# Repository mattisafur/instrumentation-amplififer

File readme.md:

# Tiny Instrumentation Amplififer

This is a small challenge I gave myself, trying to design an opamp based instrumentation amplififer while trying to make the footprint of the circuit as small as possible.

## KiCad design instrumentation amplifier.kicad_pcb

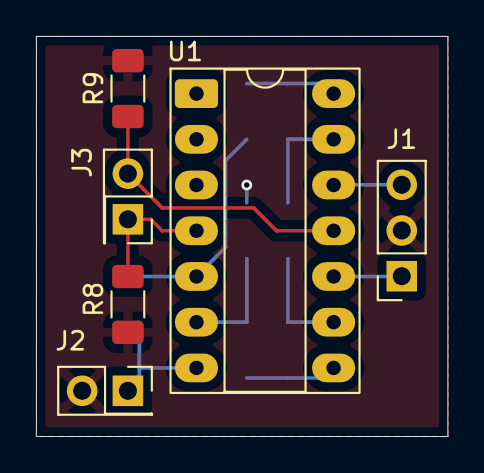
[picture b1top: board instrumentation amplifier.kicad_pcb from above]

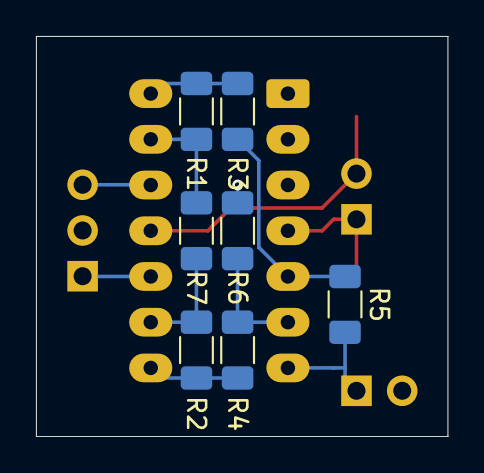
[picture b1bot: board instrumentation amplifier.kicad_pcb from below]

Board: 2 copper layers, 22.9 x 22.2 mm, 13 parts (7 on the bottom side), 12 nets.

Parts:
J1: Conn_02x02_Odd_Even; PinSocket_1x03_P2.54mm_Vertical
J2, J3: Conn_02x01; PinSocket_2x01_P2.54mm_Vertical
R1, R2, R3, R4, R5, R6, R8, R9: 10k; R_1206_3216Metric_Pad1.30x1.75mm_HandSolder
R7: R; R_1206_3216Metric_Pad1.30x1.75mm_HandSolder
U1: TL074; DIP-14_W7.62mm_Socket_LongPads

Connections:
GND: J1.2, J2.2, R6.2, R8.2, R9.1
unnamed: J1.1, U1.10 (+)
unnamed: J1.3, U1.12 (+)
unnamed: J2.1, R5.2, U1.7
unnamed: J3.1, R8.1, U1.4 (V+)
unnamed: J3.2, R9.2, U1.11 (V-)
unnamed: R1.1, R3.1, U1.14
unnamed: R2.2, R4.1, U1.8
unnamed: R3.2, R5.1, U1.5 (+)
unnamed: R4.2, R6.1, U1.6 (-)
unnamed: R2.1, R7.2, U1.9 (-)
unnamed: R1.2, R7.1, U1.13 (-)

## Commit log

2025-08-23 release v1
2025-10-14 created readme
2025-11-02 set pcb colors
2026-02-04 fix: grammar
